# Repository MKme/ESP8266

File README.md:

# Eric's ESP8266 Code & Projects
Various ESP8266 basics, functions and hardware support for incomplete projects

<p align="center">
<br>
 
 <br>
My notes projects and goodies for ESP prjects
<br>
<br>
🐦 <a href="https://twitter.com/mkmeorg">Twitter</a>
| 📺 <a href="https://www.youtube.com/mkmeorg">YouTube</a>
| 🌍 <a href="http://www.mkme.org">mkme.org</a><br>
Support this project and become a patron on <a href="http://mkme.org/patreon">Eric's Patreon</a>.<br>
Website, Forum and store are at http://mkme.org <br>
Chat with Me: <a href="https://discord.gg/j9S4Fgv">Discord</a></b>
</p>
Support this project and become a patron on <a href="http://mkme.org/patreon">Eric's Patreon</a>.<br>
Website, Forum and store are at http://mkme.org <br>
Chat with Me: <a href="https://discord.gg/j9S4Fgv">Discord</a></b>
</p>

### Discussion and further info I figure out (if any):

SD Card Use:
http://mkme.org/forum/viewtopic.php?f=14&t=1126&p=1430#p1430

### FULL Video Tutorials:

SD Card Use:
https://youtu.be/y-P627KBLBw

### BUY THE SUPPLIES HERE:

Buy a breakout board here: https://store.mkme.org/?product=wemos-d1-mini-dmb-breakout-pcb-with-screw-terminals-v1

Buy the D1 Mini here: https://amzn.to/34XAxhJ

SD Card Reader https://amzn.to/2XPDv6B

ESP01 https://amzn.to/2RSAvlR

LOLIN Variants https://amzn.to/2XSdjrP

0.96" OLED Display https://amzn.to/3cCHvvj

### SPI SD Card to WEMOS D1 Mini
| Pin On SD Reader | Pin on D1 Mini |
| ---------- |----------------|
| SCK  | D5 |
| MISO| D6 |
| MOSI  | D7 |
| CS  | D8  |
|GND   | GND |
|VCC  | 3.3V ONLY!  |

### 0.96" OLED to WEMOS D1 Mini 
| Pin On OLED | Pin on D1 Mini |
| ---------- |----------------|
| SDA  | D2 |
| SCL| D1 |
|GND   | GND |
|VCC  | 3.3V or 5V (depends on display)  |

### Useful Stuffz

More videos and information at http://youtube.com/mkmeorg or http://www.mkme.org

This work is licensed under a Creative Commons Attribution-NonCommercial 4.0 International License. https://creativecommons.org/licenses/by-nc/4.0/

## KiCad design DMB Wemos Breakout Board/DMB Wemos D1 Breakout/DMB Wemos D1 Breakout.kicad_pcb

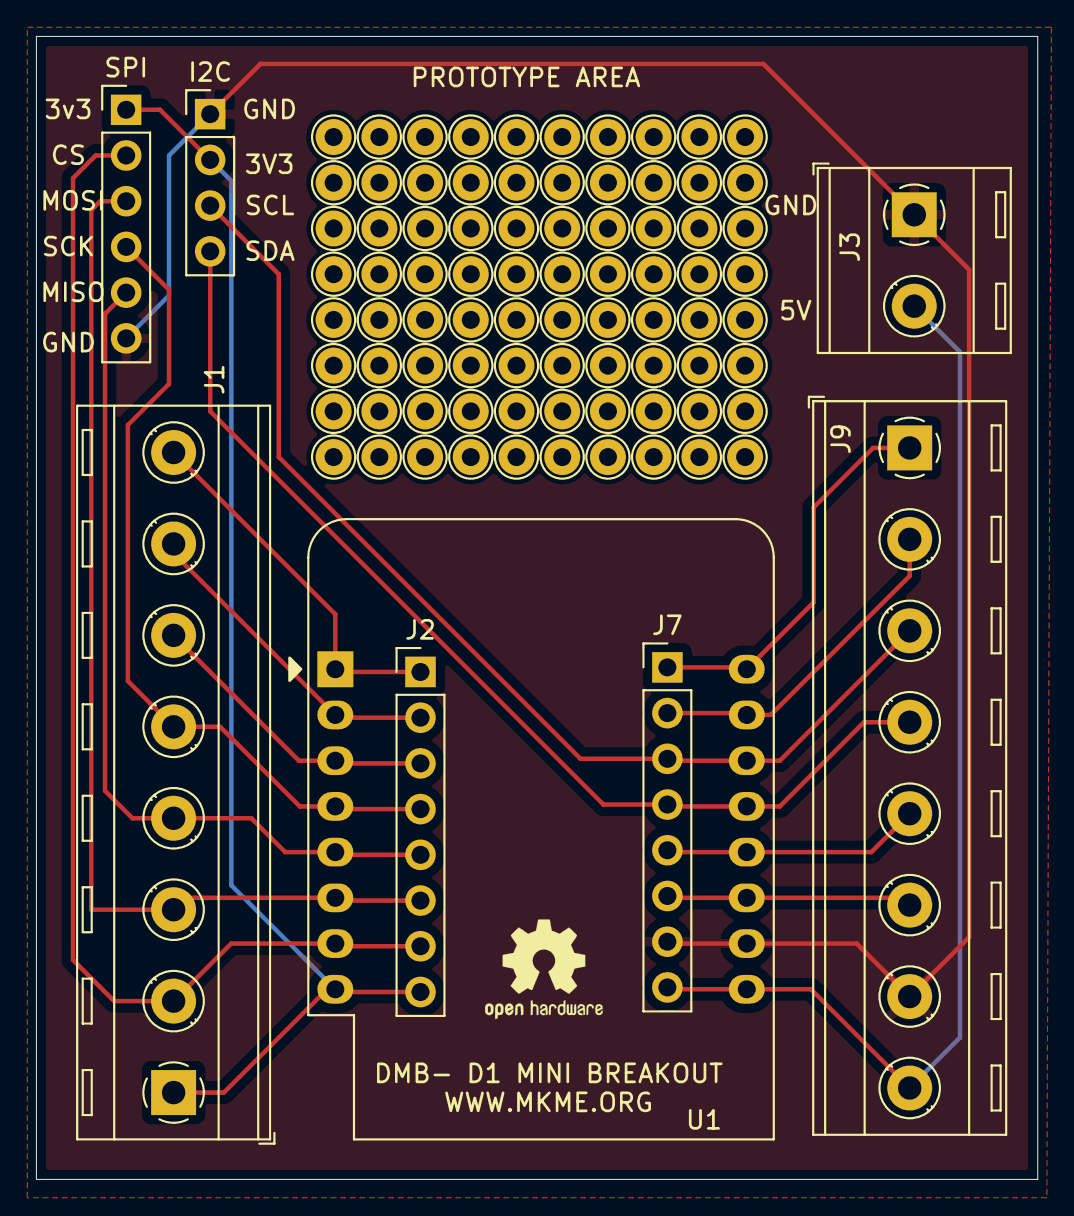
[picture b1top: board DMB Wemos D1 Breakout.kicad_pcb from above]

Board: 2 copper layers, 55.6 x 63.5 mm, 8 parts (0 on the bottom side), 16 nets.

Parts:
I2C: Conn_01x04_Male; PinHeader_1x04_P2.54mm_Vertical
J1, J9: Screw_Terminal_01x08; TerminalBlock_RND_205-00293_1x08_P5.08mm_Horizontal
J2, J7: Conn_01x08_Female; PinHeader_1x08_P2.54mm_Vertical
J3: Vin; TerminalBlock_RND_205-00287_1x02_P5.08mm_Horizontal
SPI: Conn_01x06_Male; PinHeader_1x06_P2.54mm_Vertical
U1: WeMos_D1_mini; WEMOS_D1_mini_light

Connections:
3v3: I2C.2, J1.1, J2.8, SPI.1, U1.8
5V: J3.2, J7.8, J9.8, U1.9
A0: J1.7, J2.2, U1.2
CS: J1.2, J2.7, SPI.2, U1.7
D0: J1.6, J2.3, U1.3
D3: J7.5, J9.5, U1.12
D4: J7.6, J9.6, U1.11
GND: I2C.1, J3.1, J7.7, J9.7, SPI.6, U1.10
MISO: J1.4, J2.5, SPI.5, U1.5
MOSI: J1.3, J2.6, SPI.3, U1.6
RST: J1.8, J2.1, U1.1
RX: J7.2, J9.2, U1.15
SCK: J1.5, J2.4, SPI.4, U1.4
SCL: I2C.3, J7.3, J9.3, U1.14
SDA: I2C.4, J7.4, J9.4, U1.13
TX: J7.1, J9.1, U1.16

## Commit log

2020-04-21 Added
2020-06-03 Working GPS Examples Added
2021-02-09 Boards added
2021-08-10 Final product pics
